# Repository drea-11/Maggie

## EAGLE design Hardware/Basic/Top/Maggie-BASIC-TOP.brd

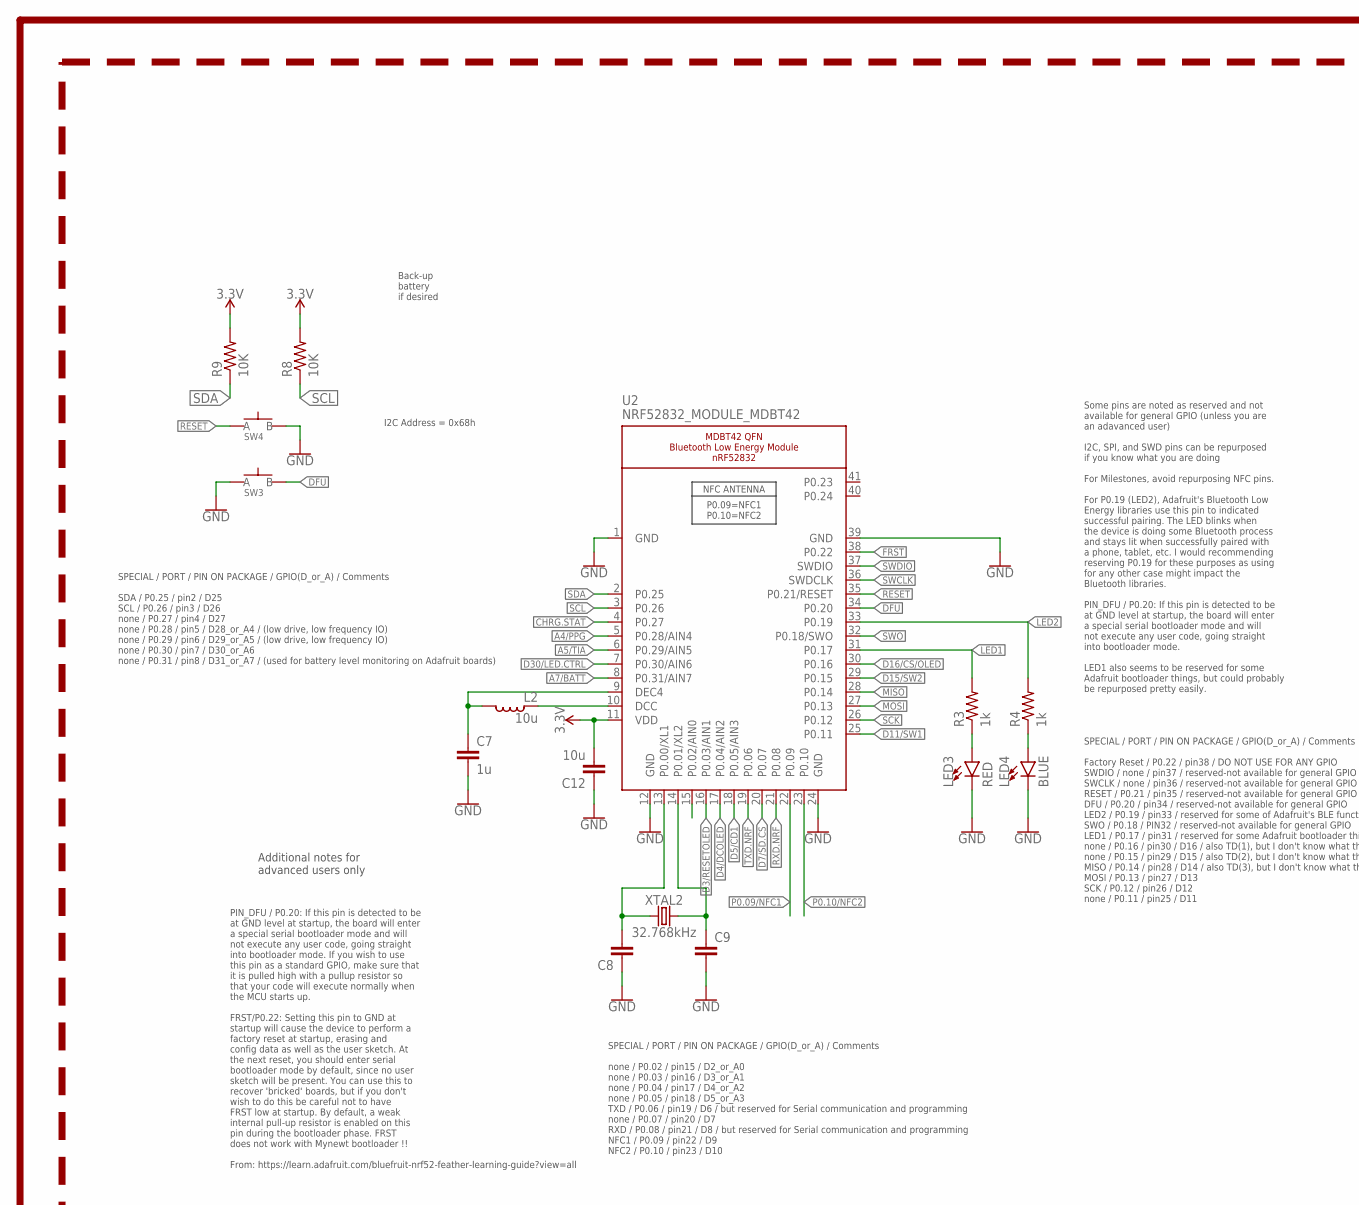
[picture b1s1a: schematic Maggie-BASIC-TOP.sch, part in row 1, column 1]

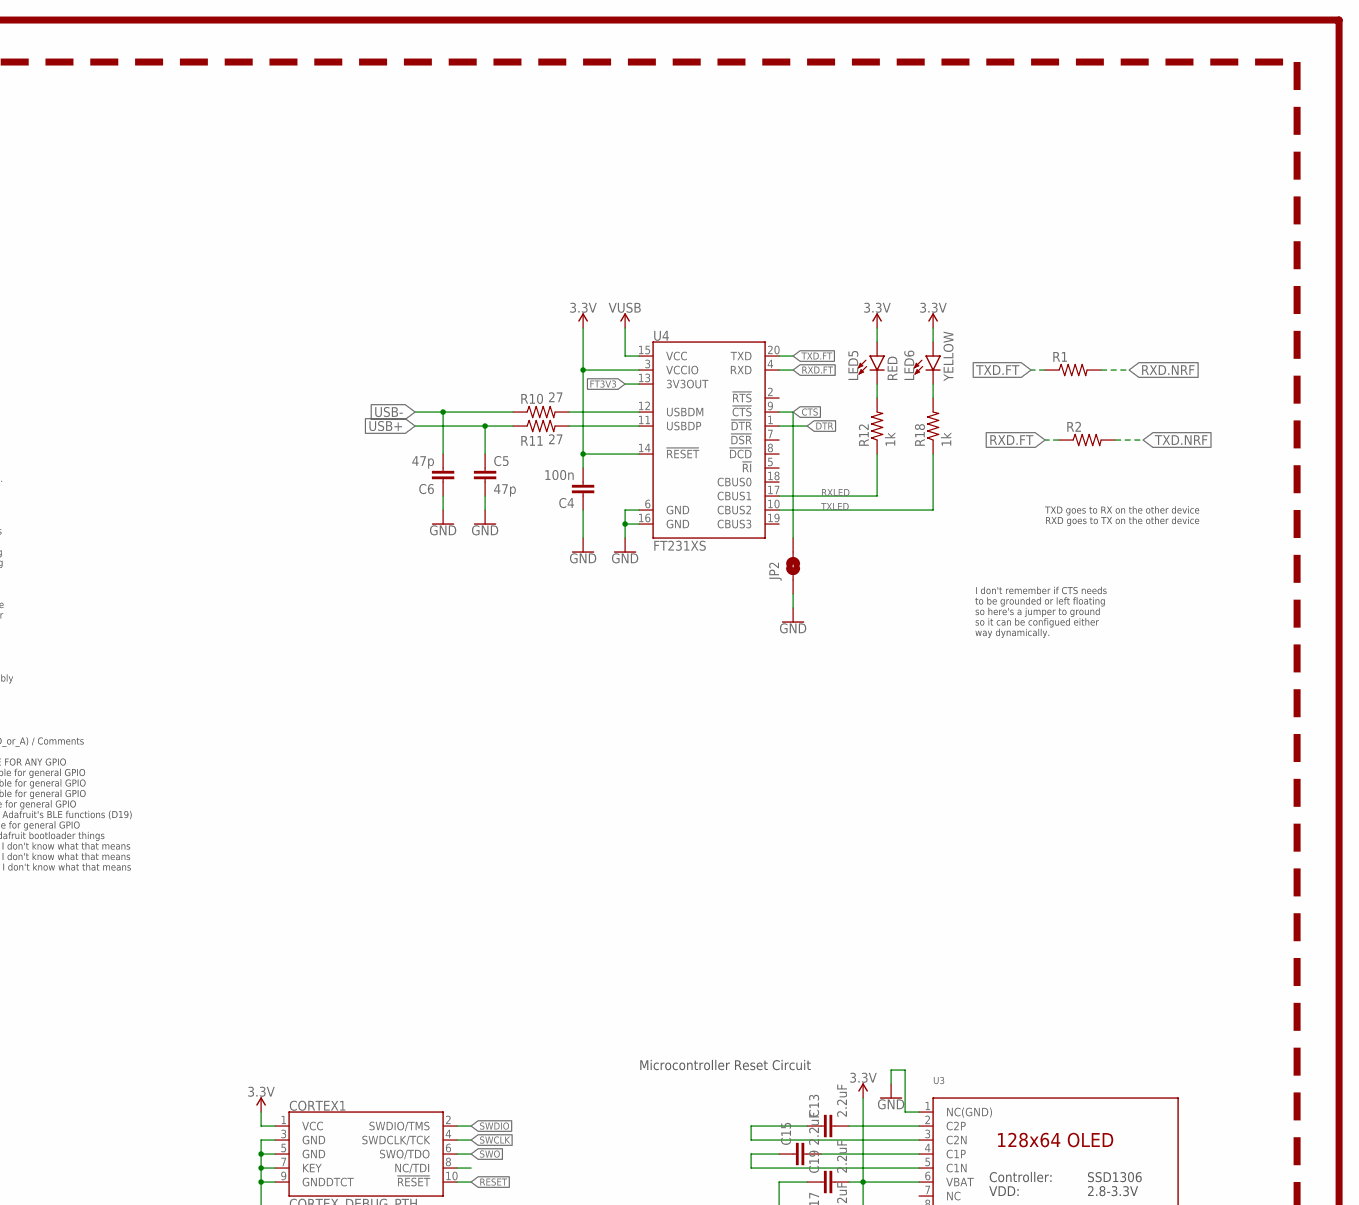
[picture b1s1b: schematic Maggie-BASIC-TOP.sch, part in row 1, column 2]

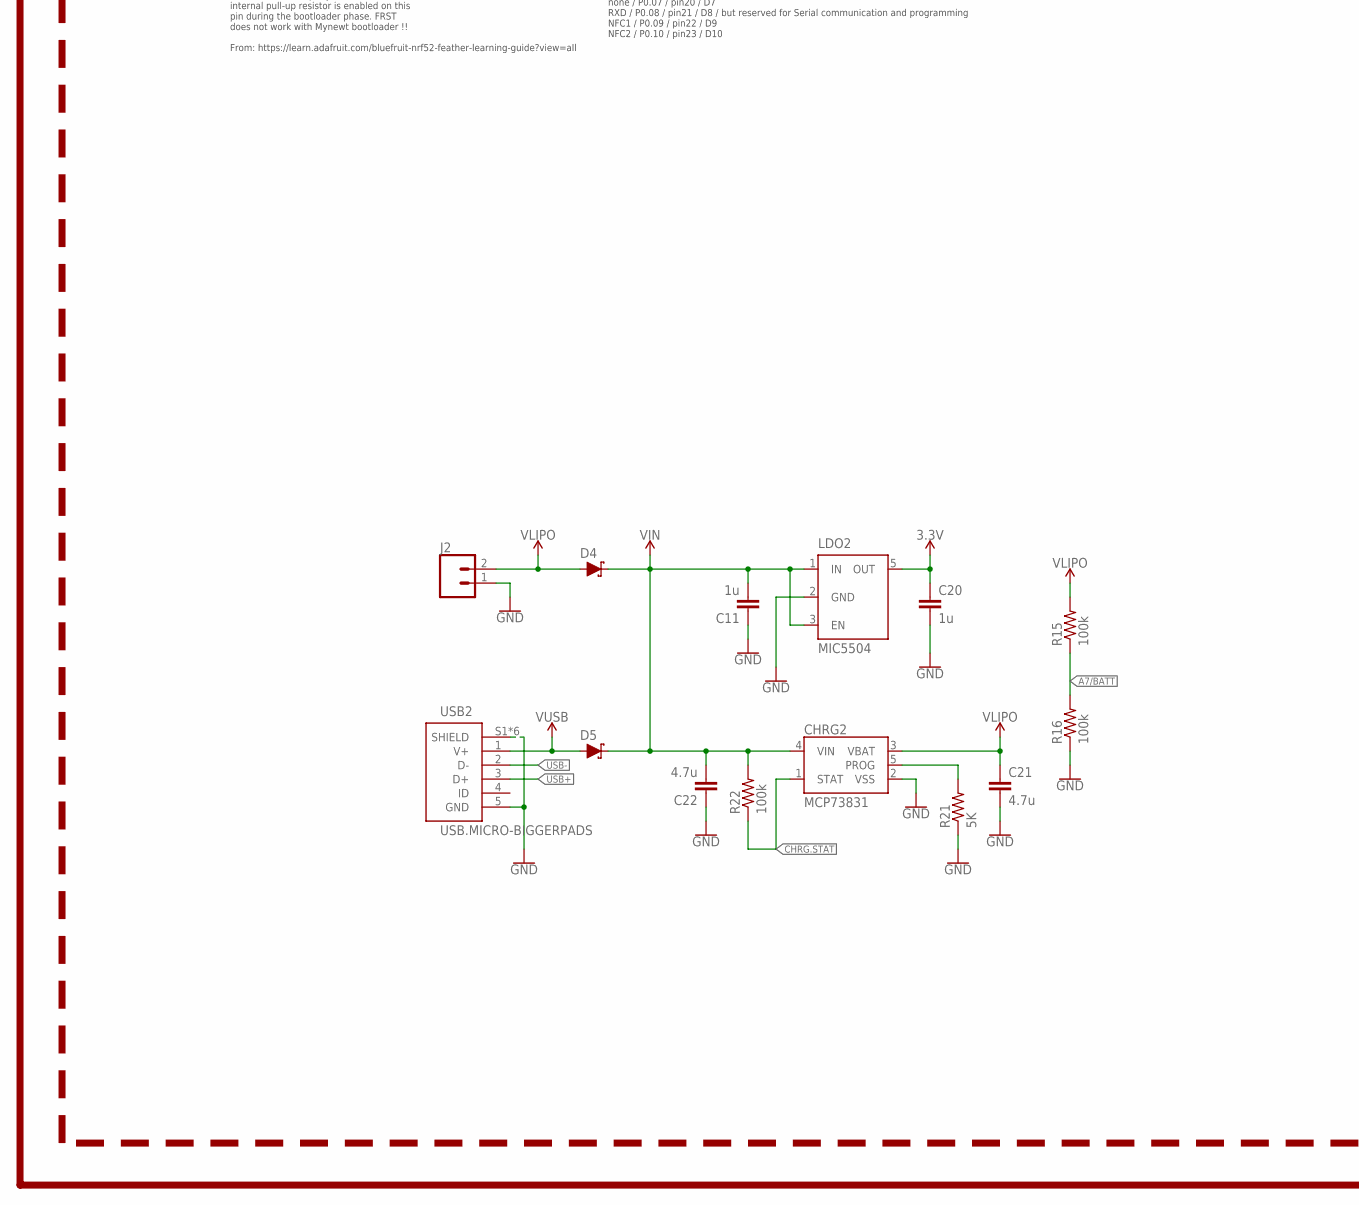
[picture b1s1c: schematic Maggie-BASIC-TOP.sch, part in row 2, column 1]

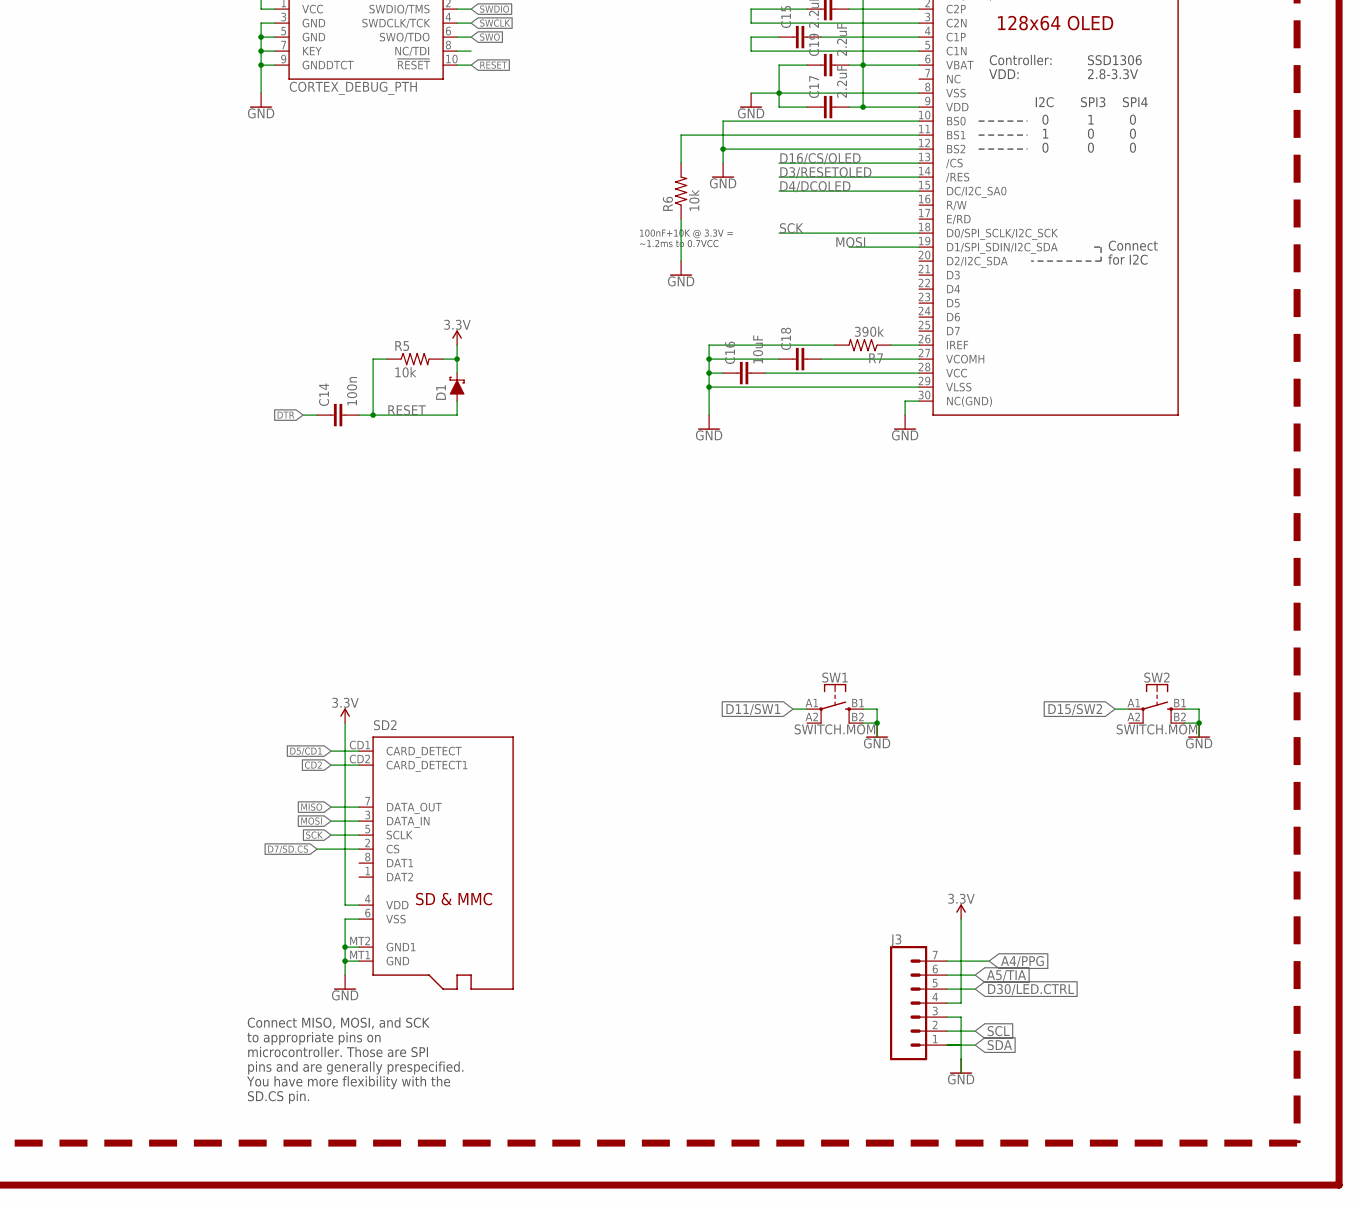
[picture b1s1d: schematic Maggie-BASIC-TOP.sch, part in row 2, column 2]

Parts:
C4, C14: 100n; C0603
C5, C6: 47p; C0603
C7, C11, C20: 1u; C0603
C8, C9, C18: CAPACITOR0603; C0603
C12: 10u; C0805
C13, C15, C17, C19: 2.2uF; C0402
C16: 10uF; C0603
C21, C22: 4.7u; C0603
CHRG2: MCP73831; SOT23-5
CORTEX1: CORTEX_DEBUG_PTH; 2X5-PTH-1.27MM
D1, D4, D5: SCHOTTKY-USC; USC
J2: CONN_02; 1X02
J3: CONN_07-1.27MM; 1X07_1.27MM
JP2: JUMPER-SMT_2_NO_SILK; SMT-JUMPER_2_NO_SILK
L2: 10u; L0603
LDO2: MIC5504; SOT23-5
LED3, LED5: RED; LED-0603
LED4: BLUE; LED-0603
LED6: YELLOW; LED-0603
R1, R2: RESISTOR0603; R0603
R3, R4, R12, R18: 1k; R0603
R5, R6: 10k; R0603
R7: 390k; R0603
R8, R9: 10K; R0603
R10, R11: 27; R0603
R15, R16, R22: 100k; R0603
R21: 5K; R0603
SD2: MICROSD
SW1, SW2: SWITCH.MOM; TACTILE_SWITCH_SMD_6.2MM_TALL
SW3, SW4: SPST-PTS830GG140-COPY.1-3; BUTTON-GULLWING
U2: NRF52832_MODULE_MDBT42; BLE_MODULE_RAYTAC_MDBT42
U3: DISP_OLED_UG-2864HSWEG01-NO-WRAPAROUND; UG-2864HSWEG01_0.96IN_NO-WRAPAROUND
U4: FT231XS; SSOP20_L
USB2: USB.MICRO-BIGGERPADS; USB-MICRO-01.BIGGERPADS
XTAL2: 32.768kHz; 2-SMD.NOLEAD.2.0MMTO1.2MM

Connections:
3.3: C4.2, C12.2, C17.2, C19.2, CORTEX1.1 (VCC), D1.- (C), LED5.A, LED6.A, R5.2, R8.2, R9.2, SD2.4 (VDD), U2.11 (VDD), U3.6 (VBAT), U3.9 (VDD), U4.3 (VCCIO), U4.14 (!RESET)
3.3V: C20.1, J3.4, LDO2.5 (OUT)
A4/PPG: J3.7, U2.5 (P0.28/AIN4)
A5/TIA: J3.6, U2.6 (P0.29/AIN5)
A7/BATT: R15.1, R16.2, U2.8 (P0.31/AIN7)
CD2: SD2.CD2 (CARD_DETECT1)
CHRG.STAT: CHRG2.1 (STAT), R22.1, U2.4 (P0.27)
CTS: JP2.2, U4.9 (!CTS)
D3/RESETOLED: U2.16 (P0.03/AIN1), U3.14 (/RES)
D4/DCOLED: U2.17 (P0.04/AIN2), U3.15 (DC/I2C_SA0)
D5/CD1: SD2.CD1 (CARD_DETECT), U2.18 (P0.05/AIN3)
D7/SD.CS: SD2.2 (CS), U2.20 (P0.07)
D11/SW1: SW1.A1 (1), U2.25 (P0.11)
D15/SW2: SW2.A1 (1), U2.29 (P0.15)
D16/CS/OLED: U2.30 (P0.16), U3.13 (/CS)
D30/LED.CTRL: J3.5, U2.7 (P0.30/AIN6)
DFU: SW3.3 (B), U2.34 (P0.20)
DTR: C14.1, U4.1 (!DTR)
FRST: U2.38 (P0.22)
FT3V3: U4.13 (3V3OUT)
GND: C4.1, C5.2, C6.1, C7.2, C8.1, C9.2, C11.1, C12.1, C16.1, C17.1, C18.1, C19.1, C20.2, C21.2, C22.1, CHRG2.2 (VSS), CORTEX1.3 (GND), CORTEX1.5 (GND), CORTEX1.7 (KEY), CORTEX1.9 (GNDDTCT), J2.1, J3.3, JP2.1, LDO2.2 (GND), LED3.C, LED4.C, R6.1, R7.2, R16.1, R21.1, SD2.6 (VSS), SD2.MT1 (GND), SD2.MT2 (GND1), SW1.B1 (3), SW1.B2 (4), SW2.B1 (3), SW2.B2 (4), SW3.1 (A), SW4.3 (B), U2.1 (GND), U2.12 (GND), U2.24 (GND), U2.39 (GND), U3.1 (NC(GND)), U3.8 (VSS), U3.10 (BS0), U3.12 (BS2), U3.29 (VLSS), U3.30 (NC(GND)), U4.6 (GND), U4.16 (GND), USB2.5 (GND), USB2.S1 (SHIELD), USB2.S2 (SHIELD), USB2.S3 (SHIELD), USB2.S4 (SHIELD), USB2.S5 (SHIELD), USB2.S6 (SHIELD)
LED1: R3.2, U2.31 (P0.17)
LED2: R4.2, U2.33 (P0.19)
MISO: SD2.7 (DATA_OUT), U2.28 (P0.14)
MOSI: SD2.3 (DATA_IN), U2.27 (P0.13), U3.19 (D1/SPI_SDIN/I2C_SDA)
unnamed: R6.2, U3.11 (BS1)
unnamed: R7.1, U3.26 (IREF)
unnamed: C13.2, U3.2 (C2P)
unnamed: C8.2, U2.13 (P0.00/XL1), XTAL2.P$1 (1)
unnamed: C13.1, U3.3 (C2N)
unnamed: C9.1, U2.14 (P0.01/XL2), XTAL2.P$2 (2)
unnamed: C15.2, U3.4 (C1P)
unnamed: C15.1, U3.5 (C1N)
unnamed: LED3.A, R3.1
unnamed: LED4.A, R4.1
unnamed: L2.1, U2.10 (DCC)
unnamed: C7.1, L2.2, U2.9 (DEC4)
unnamed: C16.2, U3.28 (VCC)
unnamed: C18.2, U3.27 (VCOMH)
unnamed: CHRG2.5 (PROG), R21.2
unnamed: R10.2, U4.12 (USBDM)
unnamed: R11.2, U4.11 (USBDP)
unnamed: LED5.C, R12.2
unnamed: LED6.C, R18.2
P0.09/NFC1: U2.22 (P0.09)
P0.10/NFC2: U2.23 (P0.10)
RESET: C14.2, CORTEX1.10 (!RESET), D1.+ (A), R5.1, SW4.1 (A), U2.35 (P0.21/RESET)
RXD.FT: R2.1, U4.4 (RXD)
RXD.NRF: R1.2, U2.21 (P0.08)
RXLED: R12.1, U4.17 (CBUS1)
SCK: SD2.5 (SCLK), U2.26 (P0.12), U3.18 (D0/SPI_SCLK/I2C_SCK)
SCL: J3.2, R8.1, U2.3 (P0.26)
SDA: J3.1, R9.1, U2.2 (P0.25)
SWCLK: CORTEX1.4 (SWDCLK/TCK), U2.36 (SWDCLK)
SWDIO: CORTEX1.2 (SWDIO/TMS), U2.37 (SWDIO)
SWO: CORTEX1.6 (SWO/TDO), U2.32 (P0.18/SWO)
TXD.FT: R1.1, U4.20 (TXD)
TXD.NRF: R2.2, U2.19 (P0.06)
TXLED: R18.1, U4.10 (CBUS2)
USB+: C5.1, R11.1, USB2.3 (D+)
USB-: C6.2, R10.1, USB2.2 (D-)
VIN: C11.2, C22.2, CHRG2.4 (VIN), D4.- (C), D5.- (C), LDO2.1 (IN), LDO2.3 (EN), R22.2
VLIPO: C21.1, CHRG2.3 (VBAT), D4.+ (A), J2.2, R15.2
V_USB: D5.+ (A), U4.15 (VCC), USB2.1 (V+)

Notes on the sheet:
Microcontroller Reset Circuit
100nF+10K @ 3.3V = ~1.2ms to 0.7VCC
SPECIAL / PORT / PIN ON PACKAGE / GPIO(D_or_A) / Comments SDA / P0.25 / pin2 / D25 SCL / P0.26 / pin3 / D26 none / P0.27 / pin4 / D27 none / P0.28 / pin5 / D28_or_A4 / (low drive, low frequency IO) none / P0.29 / pin6 / D29_or_A5 / (low drive, low frequency IO) none / P0.30 / pin7 / D30_or_A6 none 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
SPECIAL / PORT / PIN ON PACKAGE / GPIO(D_or_A) / Comments none / P0.02 / pin15 / D2_or_A0 none / P0.03 / pin16 / D3_or_A1 none / P0.04 / pin17 / D4_or_A2 none / P0.05 / pin18 / D5_or_A3 TXD / P0.06 / pin19 / D6 / but reserved for Serial communication and programming none / P0.07 / pin20 / D7 RXD / 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
SPECIAL / PORT / PIN ON PACKAGE / GPIO(D_or_A) / Comments Factory Reset / P0.22 / pin38 / DO NOT USE FOR ANY GPIO SWDIO / none / pin37 / reserved-not available for general GPIO SWCLK / none / pin36 / reserved-not available for general GPIO RESET / P0.21 / pin35 / reserved-not available for general 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
Some pins are noted as reserved and not available for general GPIO (unless you are an adavanced user) I2C, SPI, and SWD pins can be repurposed if you know what you are doing For Milestones, avoid repurposing NFC pins. For P0.19 (LED2), Adafruit's Bluetooth Low Energy libraries use this pin to indic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
PIN_DFU / P0.20: If this pin is detected to be at GND level at startup, the board will enter a special serial bootloader mode and will not execute any user code, going straight into bootloader mode. If you wish to use this pin as a standard GPIO, make sure that it is pulled high with a pullup resis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
Additional notes for advanced users only
Connect MISO, MOSI, and SCK to appropriate pins on microcontroller. Those are SPI pins and are generally prespecified. You have more flexibility with the SD.CS pin.
I2C Address = 0x68h
Back-up battery if desired
TXD goes to RX on the other device RXD goes to TX on the other device
I don't remember if CTS needs to be grounded or left floating so here's a jumper to ground so it can be configued either way dynamically.

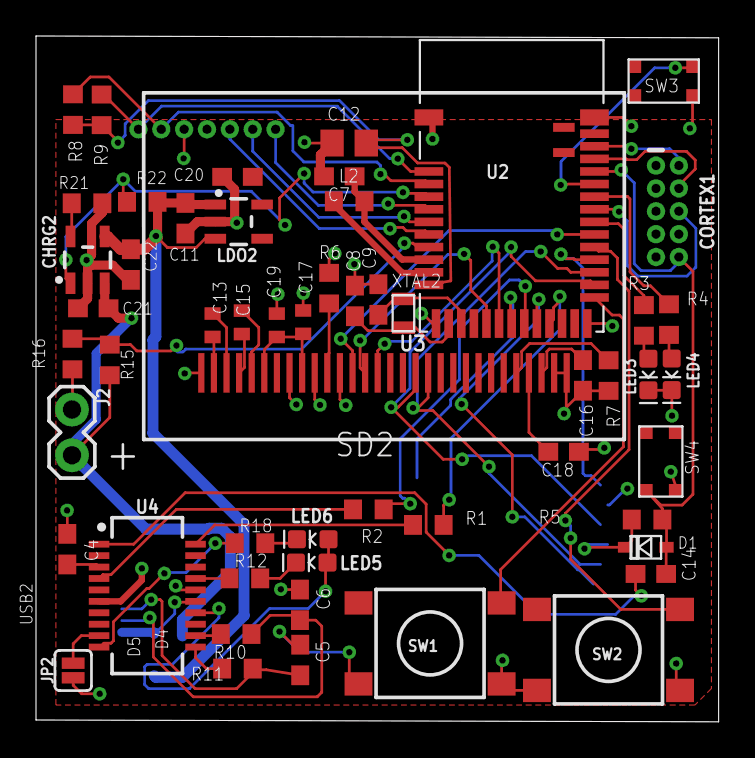
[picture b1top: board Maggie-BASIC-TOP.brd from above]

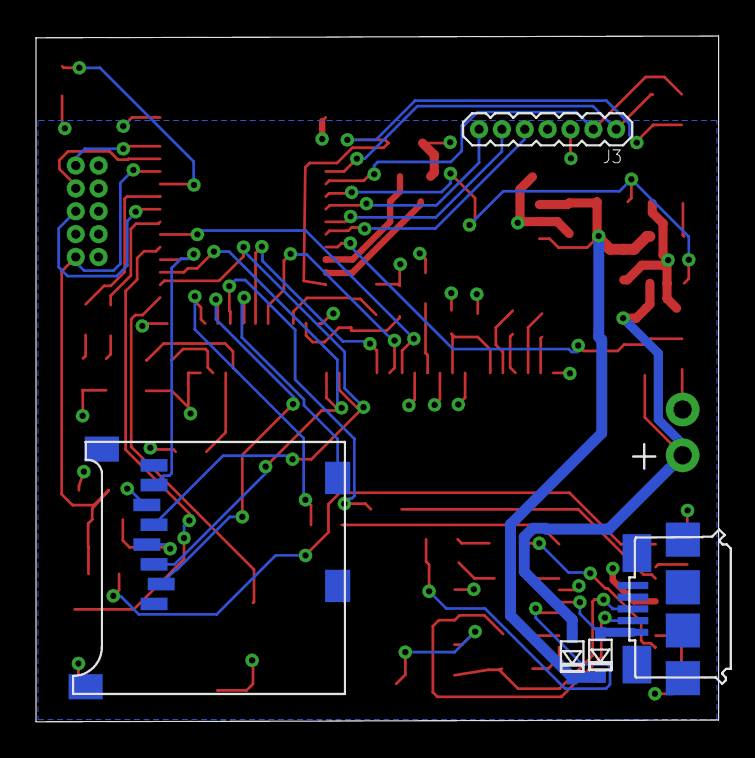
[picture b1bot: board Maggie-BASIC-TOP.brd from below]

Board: 2 copper layers, 37.9 x 38.1 mm, 59 parts (5 on the bottom side), 59 nets.

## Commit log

2020-06-30 features list
2020-07-07 firmware
2020-07-22 current
2020-07-28 check
2021-01-07 saved
